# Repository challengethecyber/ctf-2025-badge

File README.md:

# ctf-2025-badge
Badge related files for CTC 2025 CTF

## Info

- ESP32-C3-Mini
- Micropython
- E-ink display (GDEW0154M10) with UC8151 custom driver for quick partial refreshes
- IO expander (XL9535)
- EEPROM
- SAO

See schematics: [ctc_2025.pdf](hardware/ctc_2025.pdf)

## Credits

 - PCB hw design by [Max Grim](https://github.com/maxgrim).
 - Software by [c3c](https://github.com/c3c) and Max.
 - Display driver based on [GxEPD2](https://github.com/ZinggJM/GxEPD2).

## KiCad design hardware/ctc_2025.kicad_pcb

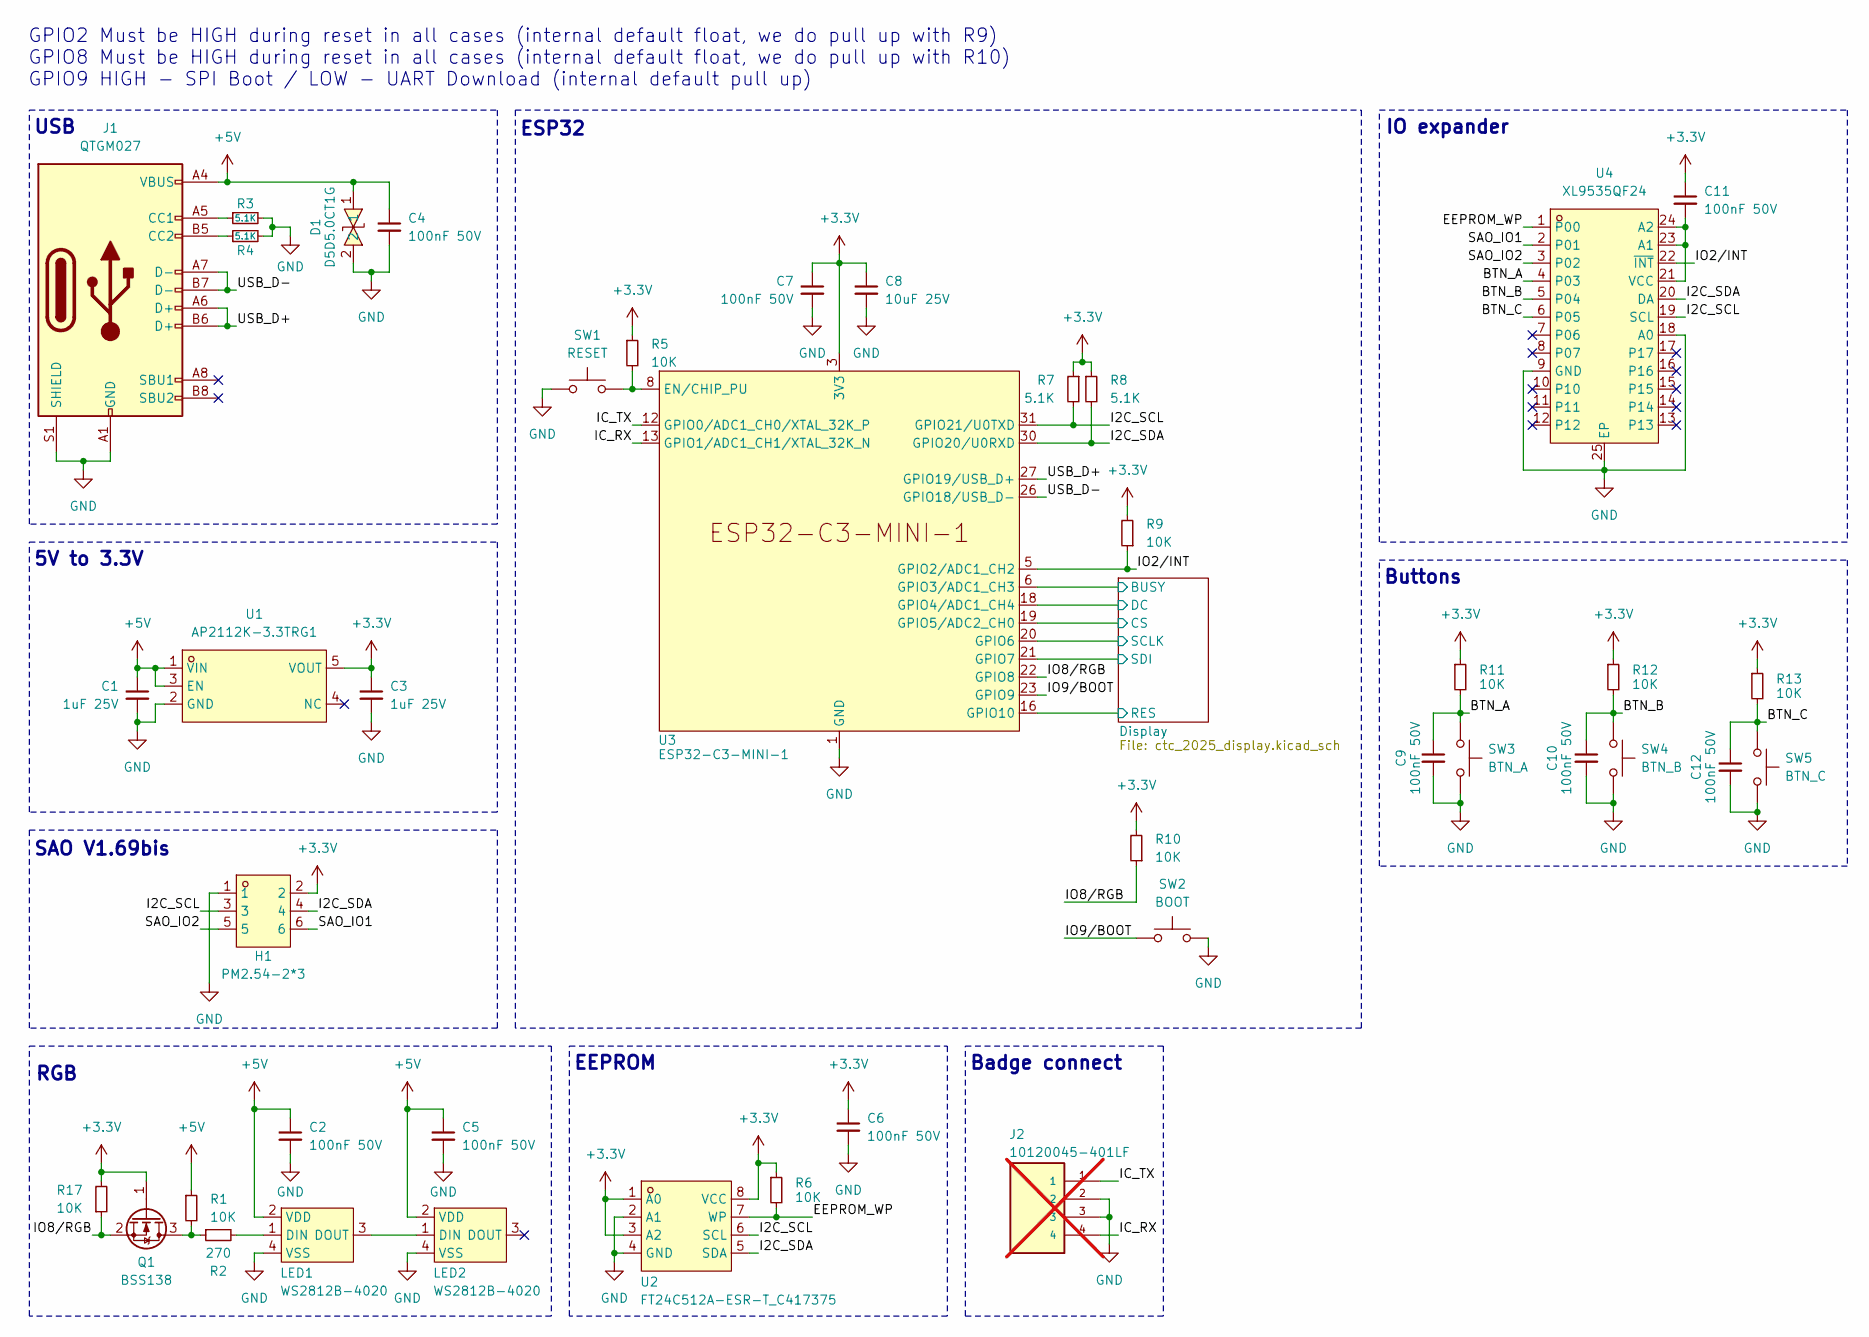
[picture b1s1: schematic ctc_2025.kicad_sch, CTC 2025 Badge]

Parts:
C1, C3: 1uF 25V; C_0402_1005Metric; LCSC Part C52923
C2, C4, C5, C6, C7, C9, C10, C11, C12: 100nF 50V; C_0402_1005Metric; LCSC Part C307331
C8: 10uF 25V; C_0603_1608Metric; LCSC Part C96446
D1: D5D5.0CT1G; SOD-523_L1.2-W0.8-LS1.6-BI; LCSC Part C383211
H1: PM2.54-2*3; HDR-TH_6P-P2.54-V-F-R2-C3-S2.54; LCSC Part C5116527
J1: QTGM027; USB-C-SMD_TYPE-C-16P-QTGM027-mod; LCSC Part C2681552
J2: 10120045-401LF; AMPHENOL_10120045-401LF; PARTREV B; not fitted
LED1, LED2: WS2812B-4020; LED-SMD_WS2812B-4020; LCSC Part C965557
Q1: BSS138; SOT-23; LCSC Part C426569
R1, R5, R6, R9, R10, R11, R12, R13, R17: 10K; R_0402_1005Metric; LCSC Part C25744
R2: 270; R_0402_1005Metric; LCSC Part C25155
R3, R4, R7, R8: 5.1K; R_0402_1005Metric; LCSC Part C25905
SW1: RESET; SW-SMD_4P-L4.2-W3.4-P2.15-LS5.2; LCSC Part C2888434
SW2: BOOT; SW-SMD_4P-L4.2-W3.4-P2.15-LS5.2; LCSC Part C2888434
SW3: BTN_A; KEY-SMD_1TS003B; LCSC Part C319395
SW4: BTN_B; KEY-SMD_1TS003B; LCSC Part C319395
SW5: BTN_C; KEY-SMD_1TS003B; LCSC Part C319395
U1: AP2112K-3.3TRG1; SOT-25-5_L2.9-W1.6-P0.95-LS2.8-BL; LCSC Part C51118
U2: FT24C512A-ESR-T_C417375; SOP-8_L4.9-W3.9-P1.27-LS6.0-BL; LCSC Part C417375
U3: ESP32-C3-MINI-1; LCSC Part C2838502
U4: XL9535QF24; QFN-24_L4.0-W4.0-P0.50-BL-EP2.6; LCSC Part C5444301

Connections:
+3.3V: C3.1, C6.1, C7.1, C8.1, C11.1, H1.2, Q1.1 (G), R5.1, R6.1, R7.1, R8.1, R9.2, R10.2, R11.1, R12.1, R13.1, R17.2, U1.5 (VOUT), U2.1 (A0), U2.3 (A2), U2.8 (VCC), U3.3 (3V3); also elsewhere on the board
/BTN_A: C9.1, R11.2, SW3.1, U4.4 (P03)
/BTN_B: C10.1, R12.2, SW4.1, U4.5 (P04)
/BTN_C: C12.1, R13.2, SW5.1, U4.6 (P05)
/Display/BUSY: U3.6 (GPIO3/ADC1_CH3); also elsewhere on the board
/Display/CS: U3.19 (GPIO5/ADC2_CH0); also elsewhere on the board
/Display/DC: U3.18 (GPIO4/ADC1_CH4); also elsewhere on the board
/Display/RES: U3.16 (GPIO10); also elsewhere on the board
/Display/SCLK: U3.20 (GPIO6); also elsewhere on the board
/Display/SDI: U3.21 (GPIO7); also elsewhere on the board
/EEPROM_WP: R6.2, U2.7 (WP), U4.1 (P00)
/I2C_SCL: H1.3, R7.2, U2.6 (SCL), U3.31 (GPIO21/U0TXD), U4.19 (SCL)
/I2C_SDA: H1.4, R8.2, U2.5 (SDA), U3.30 (GPIO20/U0RXD), U4.20 (DA)
/IC_RX: J2.4, U3.13 (GPIO1/ADC1_CH1/XTAL_32K_N)
/IC_TX: J2.1, U3.12 (GPIO0/ADC1_CH0/XTAL_32K_P)
/IO2/INT: R9.1, U3.5 (GPIO2/ADC1_CH2), U4.22 (~INT)
/IO8/RGB: Q1.2 (S), R10.1, R17.1, U3.22 (GPIO8)
/IO9/BOOT: SW2.1, SW2.2, U3.23 (GPIO9)
/SAO_IO1: H1.6, U4.2 (P01)
/SAO_IO2: H1.5, U4.3 (P02)
/USB_D+: J1.A6 (D+), J1.B6 (D+), U3.27 (GPIO19/USB_D+)
/USB_D-: J1.A7 (D-), J1.B7 (D-), U3.26 (GPIO18/USB_D-)
unnamed: J1.A5 (CC1), R3.1
unnamed: J1.B5 (CC2), R4.1
unnamed: LED1.1 (DIN), R2.2
unnamed: LED1.3 (DOUT), LED2.1 (DIN)
unnamed: Q1.3 (D), R1.2, R2.1
unnamed: R5.2, SW1.1, SW1.2, U3.8 (EN/CHIP_PU)
unnamed: C11.2, U4.21 (VCC), U4.23 (A1), U4.24 (A2)

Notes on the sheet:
USB
5V to 3.3V
ESP32
Buttons
RGB
SAO V1.69bis
EEPROM
Badge connect
IO expander
GPIO2 Must be HIGH during reset in all cases (internal default float, we do pull up with R9) GPIO8 Must be HIGH during reset in all cases (internal default float, we do pull up with R10) GPIO9 HIGH - SPI Boot / LOW - UART Download (internal default pull up)

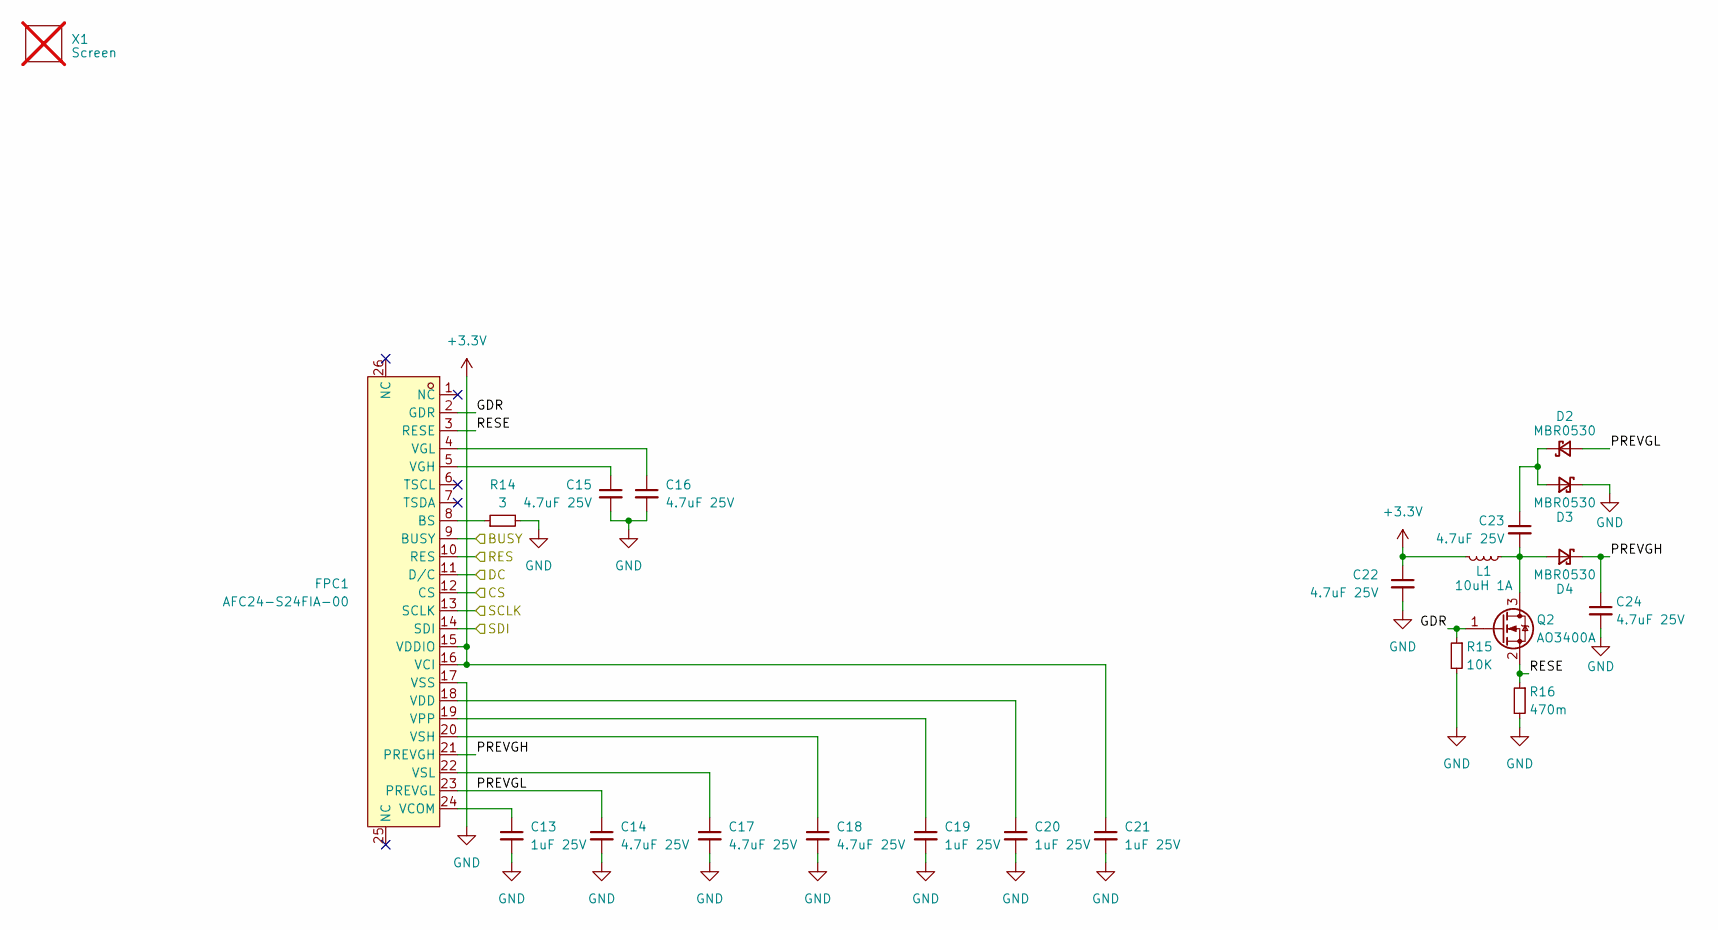
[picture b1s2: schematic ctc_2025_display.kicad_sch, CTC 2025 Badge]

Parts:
C13, C19, C20, C21: 1uF 25V; C_0402_1005Metric; LCSC Part C52923
C14, C15, C16, C17, C18, C22, C23, C24: 4.7uF 25V; C_0805_2012Metric; LCSC Part C1779
D2, D3, D4: MBR0530; D_SOD-123; LCSC Part C475718
FPC1: AFC24-S24FIA-00; FPC-SMD_P0.50-24P_QCHF-SM-H2.0-mod; LCSC Part C262683
L1: 10uH 1A; IND-SMD_L3.0-W3.0; LCSC Part C45405
Q2: AO3400A; SOT-23-3; LCSC Part C5224194
R14: 3; R_0402_1005Metric; LCSC Part C270411
R15: 10K; R_0402_1005Metric; LCSC Part C25744
R16: 470m; R_0402_1005Metric; LCSC Part C3017627
X1: Screen; not fitted

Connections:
+3.3V: C21.1, C22.1, FPC1.15 (VDDIO), FPC1.16 (VCI), L1.2; also elsewhere on the board
/Display/BUSY: FPC1.9 (BUSY); also elsewhere on the board
/Display/CS: FPC1.12 (CS); also elsewhere on the board
/Display/DC: FPC1.11 (D/C); also elsewhere on the board
/Display/GDR: FPC1.2 (GDR), Q2.1 (G), R15.1
/Display/PREVGH: C24.1, D4.1 (K), FPC1.21 (PREVGH)
/Display/PREVGL: C14.1, D2.2 (A), FPC1.23 (PREVGL)
/Display/RES: FPC1.10 (RES); also elsewhere on the board
/Display/RESE: FPC1.3 (RESE), Q2.2 (S), R16.1
/Display/SCLK: FPC1.13 (SCLK); also elsewhere on the board
/Display/SDI: FPC1.14 (SDI); also elsewhere on the board
unnamed: C23.1, D2.1 (K), D3.2 (A)
unnamed: C23.2, D4.2 (A), L1.1, Q2.3 (D)
unnamed: FPC1.8 (BS), R14.1
unnamed: C13.1, FPC1.24 (VCOM)
unnamed: C20.1, FPC1.18 (VDD)
unnamed: C15.1, FPC1.5 (VGH)
unnamed: C16.1, FPC1.4 (VGL)
unnamed: C19.1, FPC1.19 (VPP)
unnamed: C18.1, FPC1.20 (VSH)
unnamed: C17.1, FPC1.22 (VSL)

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
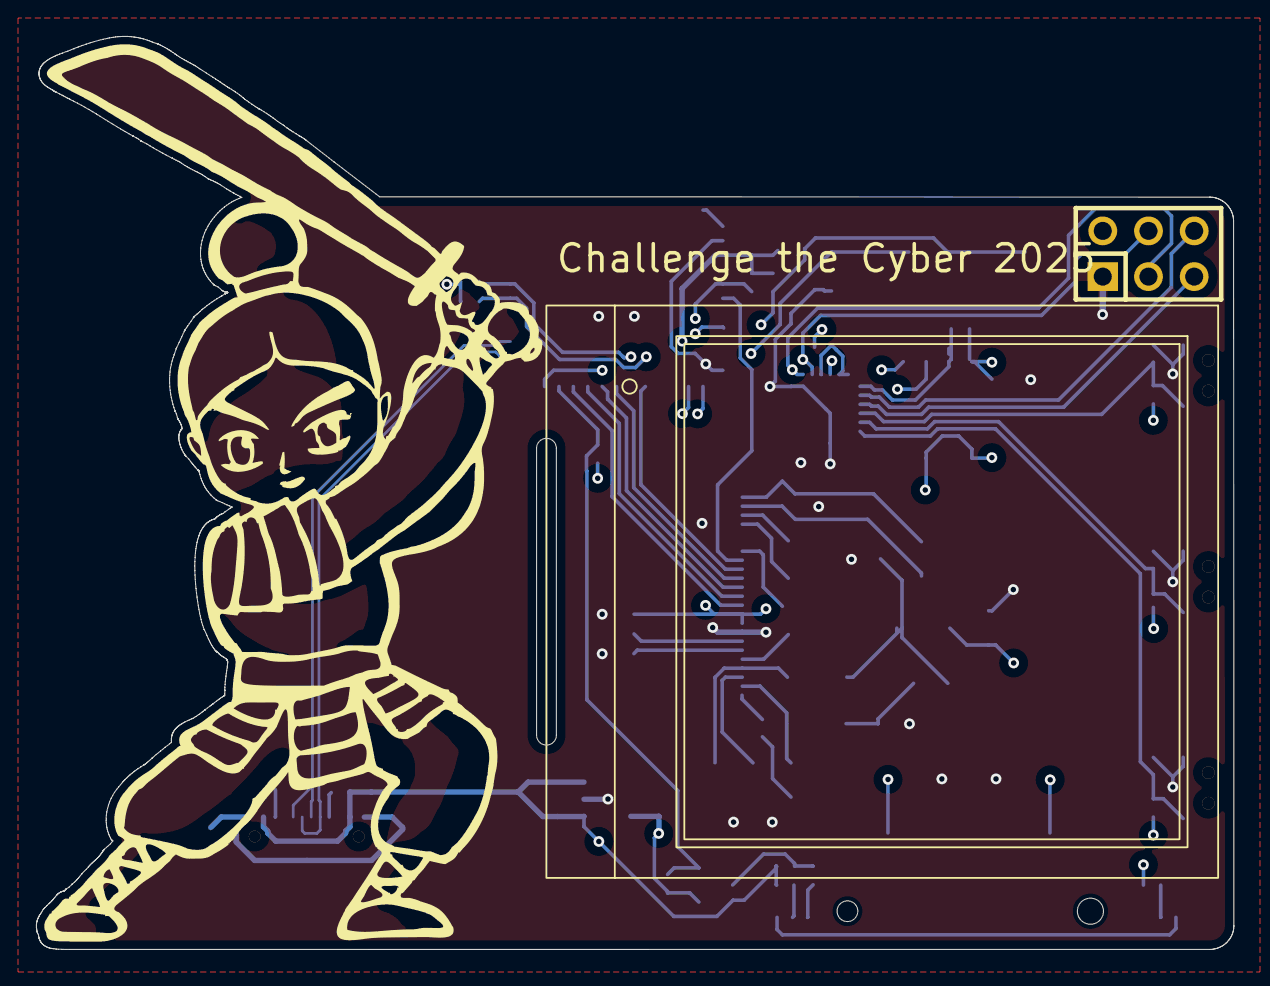
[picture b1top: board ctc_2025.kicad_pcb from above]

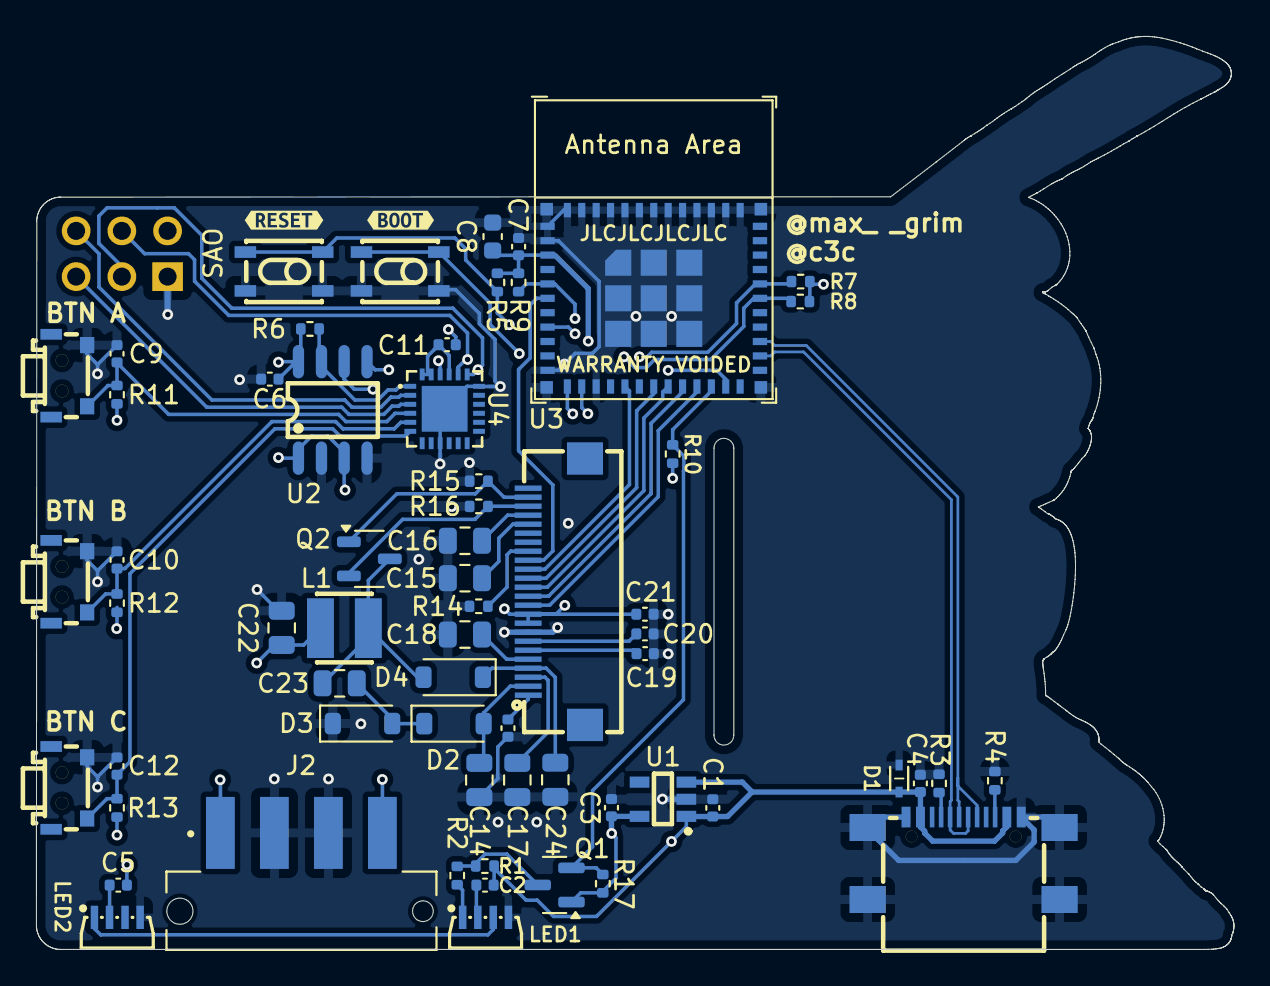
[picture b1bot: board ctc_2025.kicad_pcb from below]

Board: 4 copper layers, 66.5 x 50.7 mm, 66 parts (64 on the bottom side), 47 nets.

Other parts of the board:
kibuzzard-676D3FD4: G***; kibuzzard-676D3FD4
kibuzzard-676D3FEC: G***; kibuzzard-676D3FEC

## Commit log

2026-05-04 Enhance README with description and badge image
    Added a description and image to the README.
2026-05-04 upload
